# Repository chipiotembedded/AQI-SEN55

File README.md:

# 🌬️ ESP32 AQI Monitor with Sensirion SEN55

An advanced Air Quality Monitoring system powered by the **ESP32** and **Sensirion SEN55** sensor. This project provides real-time tracking of various environmental parameters and calculates the **Environmental Protection Agency (EPA) Air Quality Index (AQI)**.

---

## ✨ Features

- **🚀 Multi-parameter Sensing**: 
  - PM1.0, PM2.5, PM4.0, PM10 (Particulate Matter)
  - Temperature & Relative Humidity
  - VOC Index (Volatile Organic Compounds)
  - NOx Index (Nitrogen Oxides)
- **📊 Intelligent AQI Calculation**: Implements official EPA breakpoints for PM2.5, PM10, and NOx.
- **🌐 Real-time Connectivity**: 
  - MQTT Publishing via HiveMQ Broker.
  - Seamless Wi-Fi integration with auto-reconnect logic.
- **🛠️ Dual Framework Support**: Includes both **ESP-IDF** (v5.x) and **Arduino** implementations.
- **🔌 Industrial Grade Communication**: Uses Sensirion's optimized I2C drivers for high reliability.

---

## 🔌 Hardware Requirements

| Component | Description |
| :--- | :--- |
| **ESP32 Dev Board** | ESP32-WROOM, ESP32-S3, or ESP32-C3 |
| **Sensirion SEN55** | Environmental Sensor Node |
| **Wiring** | I2C (SDA/SCL), VCC (5V recommended for SEN55), GND |

### Wiring Diagram
- `SDA` → GPIO 21 (Default)
- `SCL` → GPIO 22 (Default)
- `VCC` → 5V (Note: SEN55 requires 5V for the fan, logic is 3.3V compatible)
- `GND` → GND

### 📸 Hardware Implementation
Visual overview of the physical sensor integration and circuit setup.

| **Top View** | **Side View** |
|:---:|:---:|
|  |  |

| **Assembly** | **Connection** | **Final Setup** |
|:---:|:---:|:---:|
|  |  |  |

---

## ⚙️ Software Configuration

### 1. ESP-IDF (Recommended)
Located in the `main/` directory.

Update your credentials in `main/main.c`:
```c
#define WIFI_SSID     "Your_SSID"
#define WIFI_PASSWORD "Your_Password"
```

**Build & Flash:**
```bash
idf.py set-target esp32
idf.py build
idf.py -p [PORT] flash monitor
```

### 2. Arduino IDE
Located in `aqi-sen55-ino/aqi-sen55/`.

**Dependencies:**
- `Sensirion I2C SEN5X` Library
- `PubSubClient` Library
- `WiFi` Library

---

## 📡 MQTT Data Format

Data is published as a JSON payload to the configured topic:

```json
{
  "pm1": 5.2,
  "pm2_5": 8.3,
  "pm4": 10.1,
  "pm10": 12.5,
  "temp": 25.45,
  "rh": 55.2,
  "voc": 120.5,
  "nox": 15.3,
  "aqi": 42
}
```

---

## 📈 AQI Reference Table

The project calculates AQI based on the following EPA standards:

| AQI Category | Range | PM2.5 (µg/m³) | PM10 (µg/m³) |
| :--- | :--- | :--- | :--- |
| **Good** | 0-50 | 0.0-12.0 | 0-54 |
| **Moderate** | 51-100 | 12.1-35.4 | 55-154 |
| **Unhealthy (Sens.)** | 101-150 | 35.5-55.4 | 155-254 |
| **Unhealthy** | 151-200 | 55.5-150.4 | 255-354 |
| **Very Unhealthy** | 201-300 | 150.5-250.4 | 355-424 |
| **Hazardous** | 301-500 | 250.5-500.4 | 425-604 |

---

## 📁 Project Structure

```text
├── CMakeLists.txt              Project-level CMake configuration
├── main/                       ESP-IDF Source Code
│   ├── main.c                  Application entry point & logic
│   ├── sen5x_i2c.c/.h          SEN5x sensor driver
│   └── sensirion_i2c_hal.c/.h  I2C HAL for ESP-IDF
├── aqi-sen55-ino/              Arduino Source Code
│   └── aqi-sen55/
│       └── aqi-sen55.ino       Arduino Sketch
├── pcb-designs/                Hardware design files & schematics
└── README.md                   Project documentation
```

---

## 👥 Authors

- **Anurag Doshi** (*ChipIOT Embedded System*)
- **Ashutosh Swamy**
- **Shlok Parge**
- **Aaryan Sharma**
- **Naman Vangani**

---

## 📜 Ownership

This project is owned by **ChipIOT**. Sensirion drivers are subject to their own open-source licensing.

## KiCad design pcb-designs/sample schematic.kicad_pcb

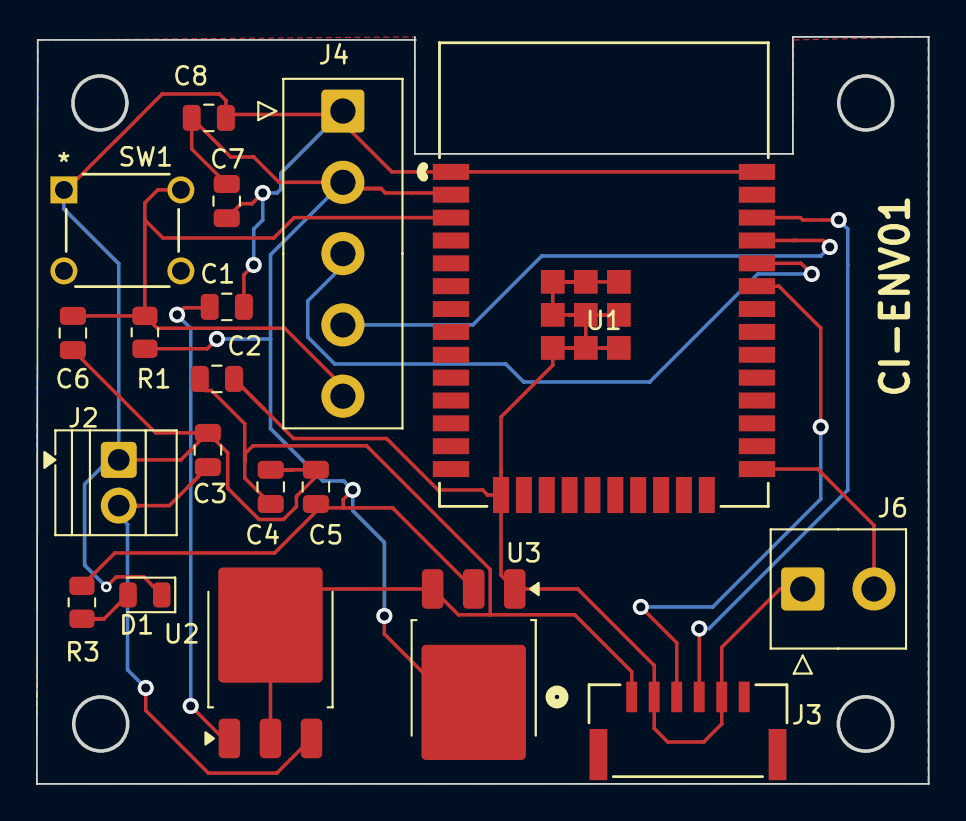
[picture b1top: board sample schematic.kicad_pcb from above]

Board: 2 copper layers, 49.5 x 41.5 mm, 19 parts (0 on the bottom side), 12 nets.

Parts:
C1, C2, C3, C5, C7: 10uf; C_0805_2012Metric
C4: 100uf; C_0805_2012Metric
C6, C8: 0.1uf; C_0805_2012Metric
D1: LED; LED_0805_2012Metric
J2: battery; TerminalBlock_Xinya_XY308-2.54-2P_1x02_P2.54mm_Horizontal
J3: SM06B-GHS-TB_LF__SN_; CONN_SM06B-GHS-TB_JST
J4: Conn_01x05_Pin; TE_826576-5_1x05_P3.96mm_Vertical
J6: Conn_01x02_Pin; TE_826576-2_1x02_P3.96mm_Vertical
R1: 10k; R_0805_2012Metric
R3: 220ohm; R_0805_2012Metric
SW1: SW_Push; SW4_1825910-D_TEC
U1: ESP32-WROOM-32; IC38_ESP32-WROOM-32 8MB_EXP
U2: LM1117DT-5.0; TO-252-3_TabPin2
U3: LM1117DT-3.3; TO-252-3_TabPin2

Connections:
+3.3V: C5.1, C7.1, C8.1, J4.2, R1.1, R3.1, U1.2 (VDD), U3.2 (VO)
+5V: C2.1, C4.1, J3.1 (VDD), U2.2 (VO), U3.3 (VI)
GND: C1.2, C2.2, C3.2, C4.2, C5.2, C6.1, C7.2, C8.2, D1.1 (K), J2.1, J3.2 (GND), J3.5 (SEL), J4.1, J6.1, SW1.1, U1.1 (GND), U1.15 (GND), U1.38 (GND), U1.39 (GND), U1.40, U1.41, U1.42, U1.43, U1.44, U1.45, U1.46, U1.47, U3.1 (GND)
unnamed: D1.2 (A), R3.2
unnamed: C3.1, J2.2, U2.3 (VI)
unnamed: J3.4 (SCL), U1.36 (IO22)
unnamed: J3.3 (SDA), U1.33 (IO21)
unnamed: J4.3, U1.34 (RXD0/IO3)
unnamed: J4.4, U1.35 (TXD0/IO1)
unnamed: C6.2, J4.5, R1.2, SW1.2, U1.3 (EN)
unnamed: J6.2, U1.25 (IO0)
unnamed: C1.1, U2.1 (GND)

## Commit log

2026-01-16 added multiple wifi networks 🚀
2026-02-07 changed to one network 🚀
2026-05-15 uploaded pcb designs and code 🚀
2026-05-15 added project images 🚀
2026-06-22 Create Documents
